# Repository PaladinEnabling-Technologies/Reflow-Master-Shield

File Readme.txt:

Readme
:
*******

1. Congratulations if you've purchased an Paladin Enabling Technologies solder reflow shield / controller, 
   if you decide to make it yourself, goodluck.

2. Before we can start reflowing your boards you will have to first load the EEPROM Population sketch onto the board,
   this is to move the default values into the EEPROM and to save you some time programming it in by hand.

3. If your not using an Arduino UNO but an Arduino Mega, then you will have to copy a replacement config file
   into your openGLCD library folder so that the shield will work.

4. The file is found in the "Master Config File - Same Pinout for all boards" folder and must be copied to the
   "C:\Program Files\Arduino\libraries\openGLCD" folder if this is your installation path of your Arduino IDE.

5. You can replace this file with the original master config file found in the "Master Config File - Original"
   folder if your not going to use the shield anymore and would like to use the default pinout for the Arduino Mega,

6. Next we can load the main Solder Reflow Oven Coding Sketch onto your board. There are two versions available. One for
   the UNO and one for the MEGA. 

7. Please note that the default values are for the toaster oven that we have used,
   you might have to adjust it for the oven your using as well as for the solder paste.

8. Please note that when you're in a submenu, you can navigate through it by pressing the ENT button.
   You can't escape so you must navigate through the menu. (You will notice that the "ESC" will disappear if you need to 
   navigate through a submenu)

9. Please read through the additional documentation in the sketches.

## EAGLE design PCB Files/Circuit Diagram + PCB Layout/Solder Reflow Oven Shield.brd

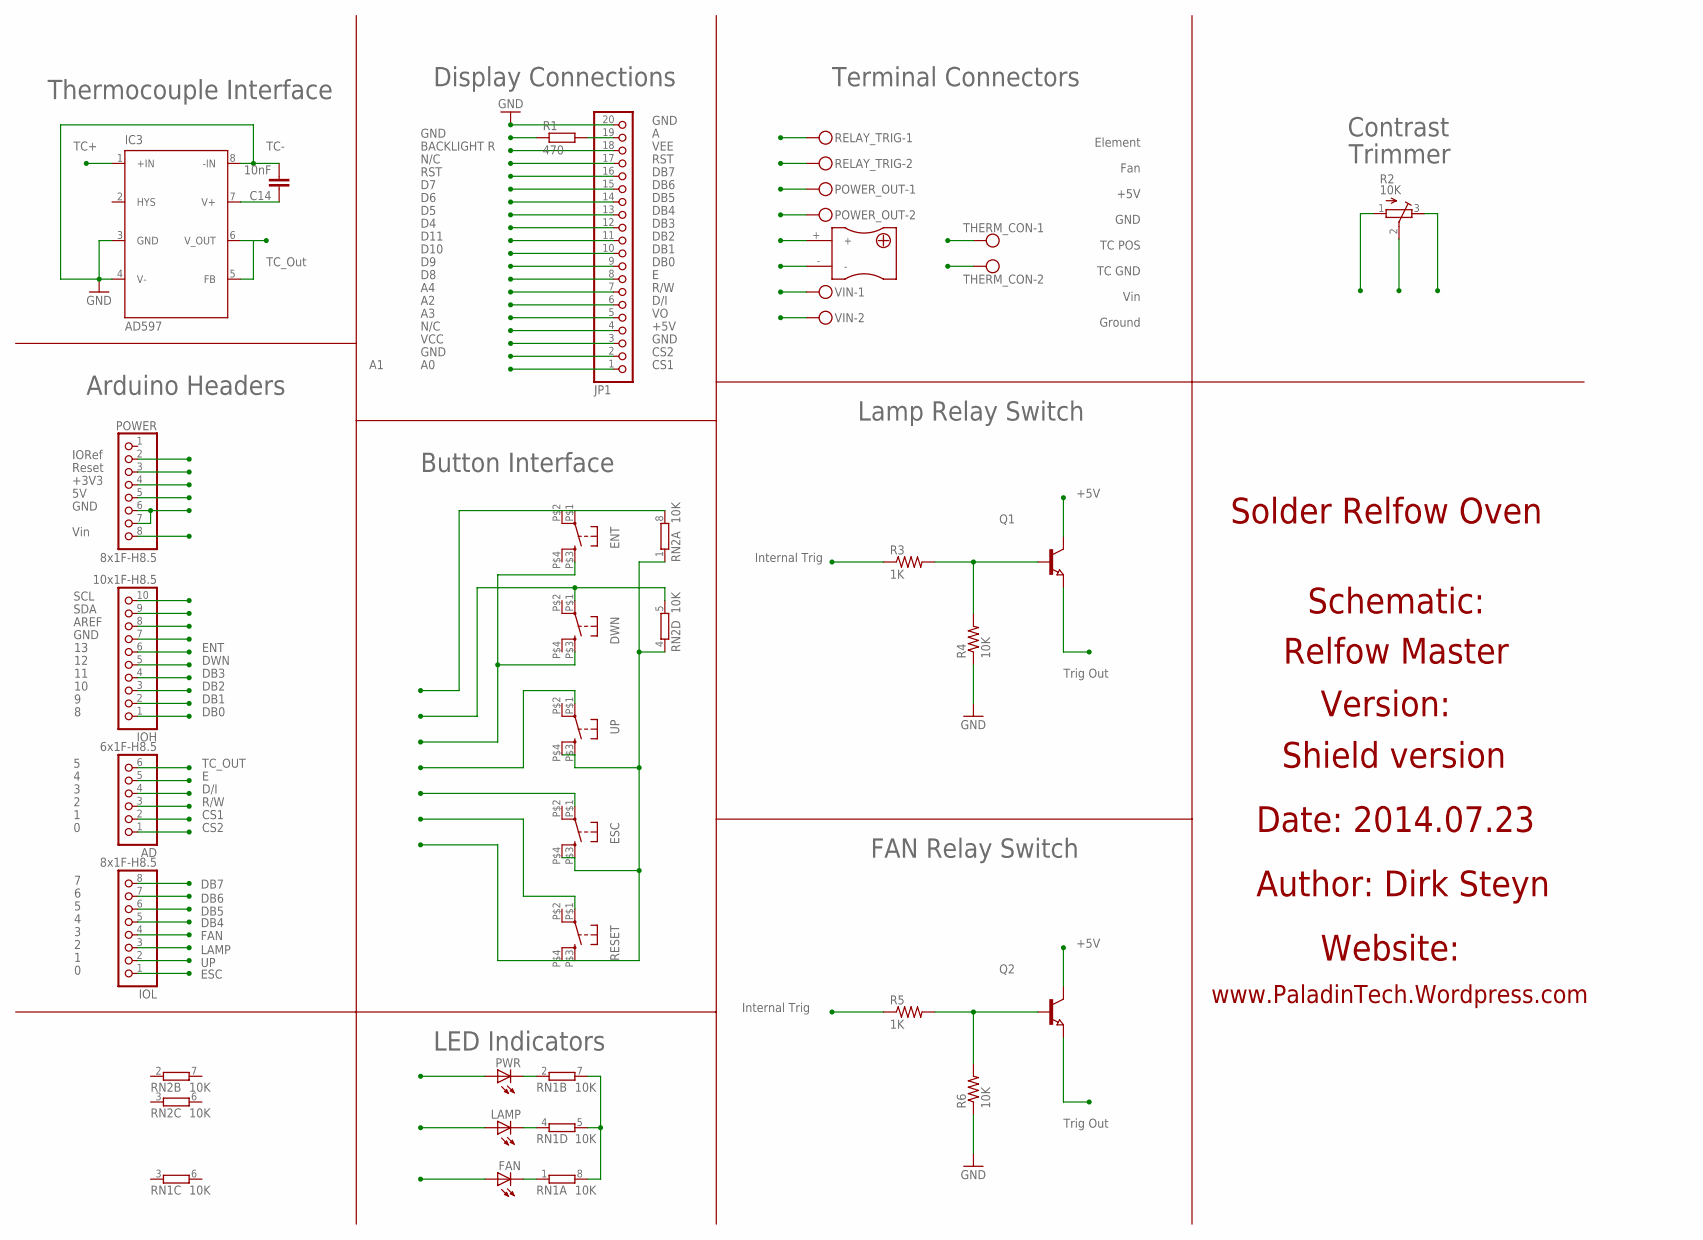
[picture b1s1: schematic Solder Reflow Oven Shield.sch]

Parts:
AD: 6x1F-H8.5; 1X06
C14: 10nF; C0603
DWN: MANTECH_TAC
ENT: MANTECH_TAC
ESC: MANTECH_TAC
FAN: LEDCHIP-LED0603; CHIP-LED0603
IC3: AD597; SO8
IOH: 10x1F-H8.5; 1X10
IOL: 8x1F-H8.5; 1X08
JP1: PINHD-1X20; 1X20
LAMP: LEDCHIP-LED0603; CHIP-LED0603
POWER: 8x1F-H8.5; 1X08
POWER_OUT: MKDSN1,5/2-5,08; 2XPCB_TER
PWR: LEDCHIP-LED0603; CHIP-LED0603
Q1, Q2: NPN-TRANSISTOR_SOT23; SOT23
R1: 470; R0603
R2: 10K; MURATA_PVZ3A
R3, R5: 1K; R0603
R4, R6: 10K; R0603
RELAY_TRIG: MKDSN1,5/2-5,08; 2XPCB_TER
RESET: MANTECH_TAC
RN1, RN2: 10K; EXB38V
THERM_CON: MKDSN1,5/2-5,08; 2XPCB_TER
U$1: THERMOCOUPLEPLUG_MINI; TC-MINI
UP: MANTECH_TAC
VIN: MKDSN1,5/2-5,08; 2XPCB_TER

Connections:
+3V3: POWER.4
+5V: C14.1, DWN.P$3 (3), ENT.P$3 (3), IC3.7 (V+), JP1.4, POWER.5, POWER_OUT.1, PWR.A, Q1.3 (C), Q2.3 (C), R1.1
A: JP1.19, R1.2
AREF: IOH.8
CS1: AD.2, JP1.1
CS2: AD.1, JP1.2
D/I: AD.4, JP1.6
DB0: IOH.1, JP1.9
DB1: IOH.2, JP1.10
DB2: IOH.3, JP1.11
DB3: IOH.4, JP1.12
DB4: IOL.5, JP1.13
DB5: IOL.6, JP1.14
DB6: IOL.7, JP1.15
DB7: IOL.8, JP1.16
DWN: DWN.P$1 (1), IOH.5, RN2.5 (2)
E: AD.5, JP1.8
ELEMENT_OUT: Q1.2 (E), RELAY_TRIG.1
ENT: ENT.P$1 (1), ENT.P$2 (2), IOH.6, RN2.8 (2)
ESC: ESC.P$1 (1), IOL.1
FAN: FAN.A, IOL.4, R5.1
FAN_OUT: Q2.2 (E), RELAY_TRIG.2
GND: C14.2, ESC.P$3 (3), ESC.P$4 (4), IC3.3 (GND), IC3.4 (V-), IC3.8 (-IN), IOH.7, JP1.3, JP1.20, POWER.6, POWER.7, POWER_OUT.2, R2.3, R4.1, R6.1, RESET.P$3 (3), RESET.P$4 (4), RN1.5 (2), RN1.7 (2), RN1.8 (2), RN2.1, RN2.4 (1), THERM_CON.2, U$1.-, UP.P$3 (3), UP.P$4 (4), VIN.2
IOREF: POWER.2
LAMP: IOL.3, LAMP.A, R3.1
unnamed: LAMP.C, RN1.4 (1)
unnamed: PWR.C, RN1.2 (1)
unnamed: FAN.C, RN1.1
unnamed: Q1.1 (B), R3.2, R4.2
unnamed: Q2.1 (B), R5.2, R6.2
R/W: AD.3, JP1.7
RST: JP1.17, POWER.3, RESET.P$1 (1)
SCL: IOH.9
SDA: IOH.10
TC+: IC3.1 (+IN), THERM_CON.1, U$1.+
TC_OUT: AD.6, IC3.5 (FB), IC3.6 (V_OUT)
UP: IOL.2, UP.P$1 (1)
VEE: JP1.18, R2.1
VIN: POWER.8, VIN.1
VO: JP1.5, R2.2

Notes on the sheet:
SDA
SCL
AREF
Fan
GND
Ground
Vin
TC POS
TC GND
Reset
+3V3
Element
+5V
ESC
LAMP
FAN
DB4
DB5
DB6
DB7
ENT
DWN
DB3
DB2
DB1
DB0
TC_OUT
D/I
R/W
CS2
CS1
IORef
Display Connections
Thermocouple Interface
LED Indicators
Arduino Headers
Button Interface
FAN Relay Switch
Lamp Relay Switch
Contrast

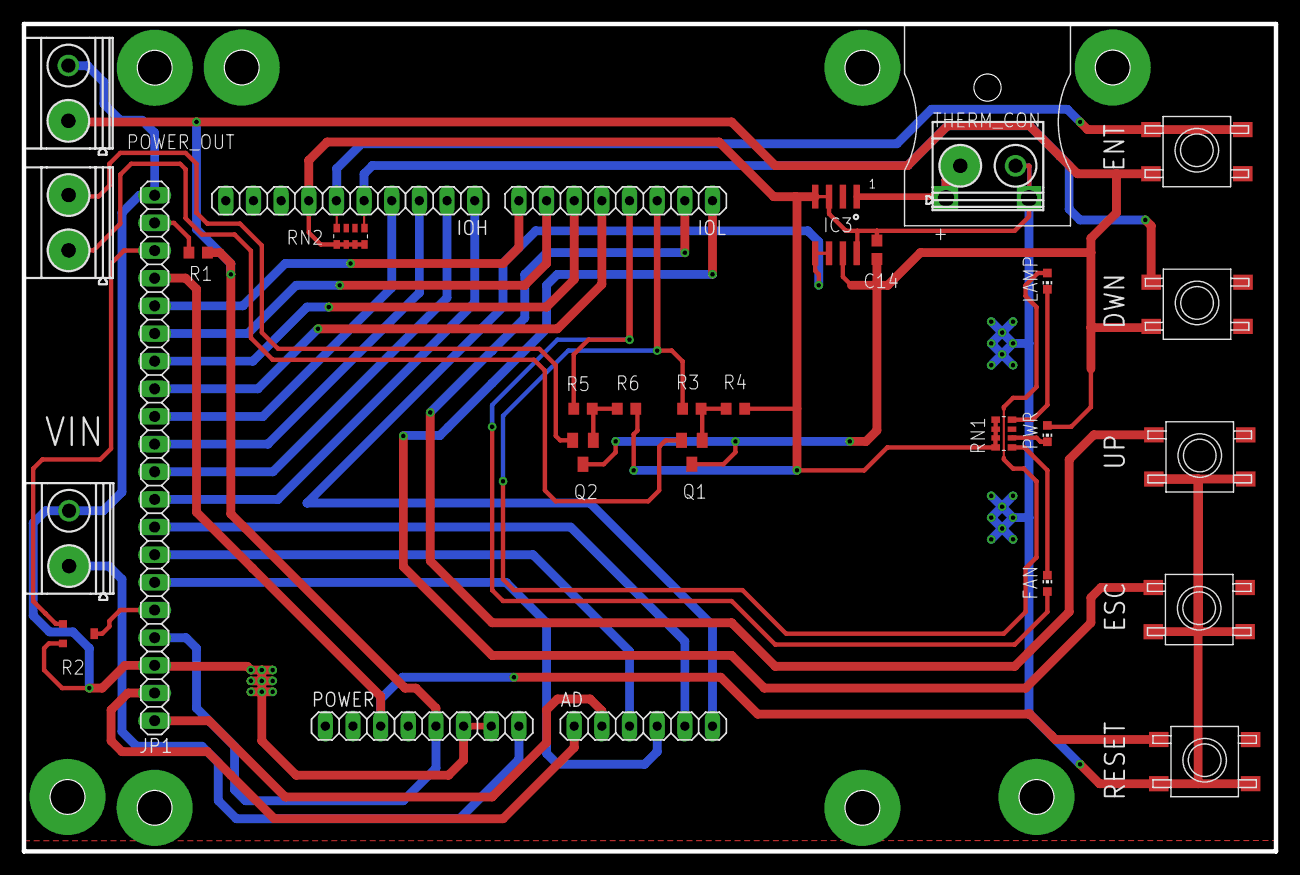
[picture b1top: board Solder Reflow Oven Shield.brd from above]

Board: 2 copper layers, 115.0 x 76.0 mm, 30 parts (0 on the bottom side), 35 nets.

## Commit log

2014-10-11 :octocat: Added .gitattributes & .gitignore files
2014-10-11 Reflow Master Shied
    Paladin Enabling Technologies
    Reflow Master Shield
    Circuit diagram, firmware, configuration files, variable explanation
    readme and general readme
    Enjoy
2016-10-10 Circuit diagram, PCB design + Gerber Files
2016-10-10 Changed files to include everything
    Uploaded all the relevant files to be able to recreate this project by yourself. This includes the code, circuit diagram, PCB design, Gerber files etc.
